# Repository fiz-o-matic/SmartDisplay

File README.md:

# SmartDisplay

Project Page: https://fiz-o-matic.net/
Wiki: https://wiki.fiz-o-matic.net/doku.php/smartdisplay:einbauanleitung
Shop: https://shop.fiz-o-matic.net/SmartDisplay/

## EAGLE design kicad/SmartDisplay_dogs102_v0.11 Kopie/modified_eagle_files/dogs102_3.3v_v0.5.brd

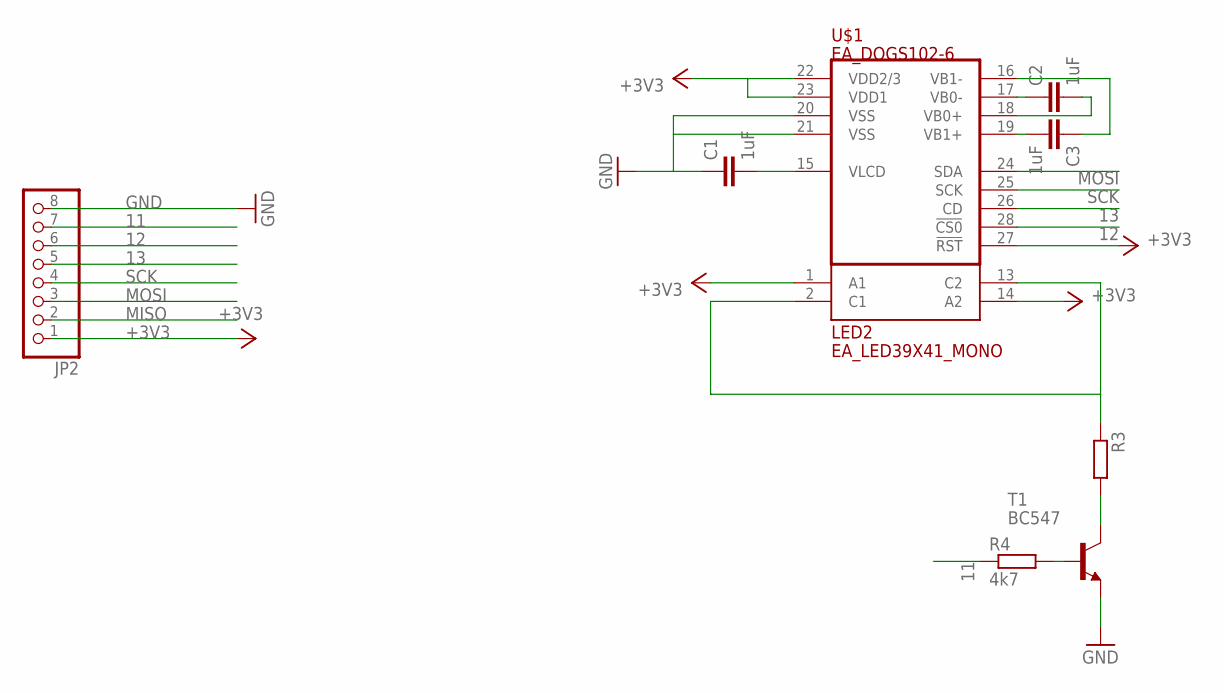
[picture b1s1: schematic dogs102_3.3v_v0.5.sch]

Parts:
C1, C2, C3: 1uF; C050-035X075
JP2: PINHD-1X8; 1X08
LED2: EA_LED39X41_MONO; EA_LED39X41
R3: R-EU_0204/2V; 0204V
R4: 4k7; 0204V
T1: BC547; TO92-CBE
U$1: EA_DOGS102-6

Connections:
11: JP2.7, R4.1
12: JP2.6, U$1.28 (!CS0!)
13: JP2.5, U$1.26 (CD)
+3V3: JP2.1, LED2.1 (A1), LED2.14 (A2), U$1.22 (VDD2/3), U$1.23 (VDD1), U$1.27 (!RST!)
GND: C1.1, JP2.8, T1.E, U$1.20 (VSS), U$1.21 (VSS)
LCD_LED_OUT: LED2.2 (C1), LED2.13 (C2), R3.1
MISO: JP2.2
MOSI: JP2.3, U$1.24 (SDA)
unnamed: C2.1, U$1.17 (VB0-)
unnamed: C2.2, U$1.18 (VB0+)
unnamed: C3.2, U$1.19 (VB1+)
unnamed: C3.1, U$1.16 (VB1-)
unnamed: C1.2, U$1.15 (VLCD)
unnamed: R3.2, T1.C
unnamed: R4.2, T1.B
SCK: JP2.4, U$1.25 (SCK)

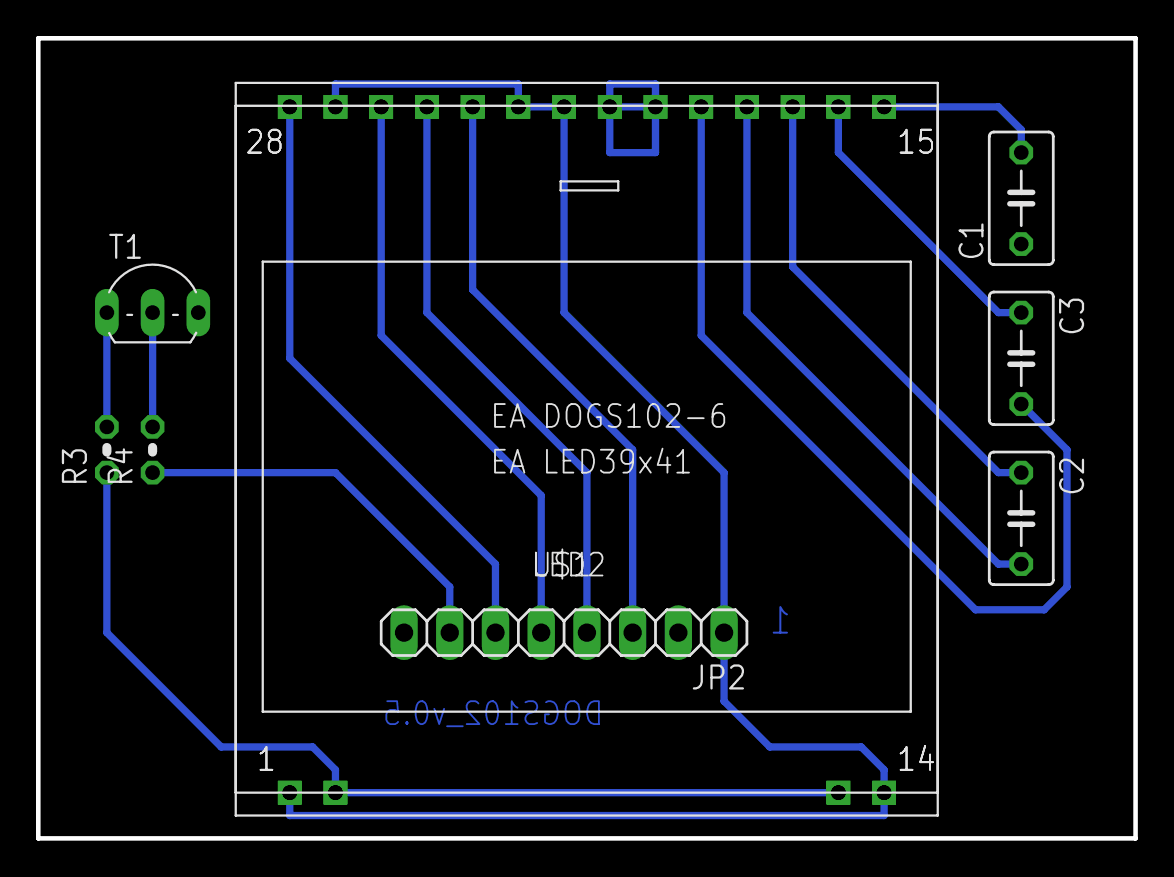
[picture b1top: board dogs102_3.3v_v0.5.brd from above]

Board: 2 copper layers, 61.0 x 44.5 mm, 9 parts (0 on the bottom side), 15 nets.

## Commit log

2022-08-19 first push
2022-08-19 first comit
2023-01-11 added trip reset function
2023-01-12 add trip reset function
2023-01-13 add GPS_SPEED_OFFSET
2023-06-23 save trip to eeprom
2023-06-23 remove debugs
2023-06-27 add gps speed to check running engine
2023-07-03 don't diplay temperature if no sensor is found
2023-11-13 update to latest version
2024-02-19 add can functions
2024-03-16 add watchdog for GPS module
2024-05-08 init upload
2024-05-08 test
2024-05-08 branche test
2024-05-08 added content
2024-05-09 removed unused files
2024-05-09 update gitignore
2024-05-09 update to 20240509
2024-05-09 add branche 0.9.2
2024-05-09 commit version 0.9.3
2024-05-09 removed nointerrupts()
2024-05-10 improve first key press
2024-05-10 add build.sh
2024-05-16 moved config to .ino file
2024-05-16 little bit cleanup
2024-05-16 remove bug in Trip EEPROM write
2024-05-16 optimize debugging
2024-06-19 removed unused lib
2024-06-22 remove platform copy.ini
2024-07-31 update trip only if >1km
2024-09-06 test Adafruit UPDI
